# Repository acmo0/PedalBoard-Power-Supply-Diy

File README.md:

# PedalBoard-Alimentation
***
## Table of contents
1. [230V Schematic](#230v-schematic)
2. [Diode Bridge Schematic](#diode-bridge-schematic)
3. [Regulated ouput Schematic](#regulated-output-schematic)
    1. [9V Output](#9v-output)
    2. [9-12V Output](#9-12v-output)
8. [Replicate Project](#replicate-project)
    1. [10 Outputs (7x9v + 3x9-12v) Version](#10-outputs-version)
    2. [7 Outputs (7x9v) Version](#7-outputs-version)
    3. [Custom power supply](#custom-power-supply)
7. [Kicad sources files](#Kicad-sources-files)
8. [Issues](#issues)
***
## 230V Schematic

This is a basic schematic in order to protect your pedalboard against surges (VDR), short-circuit (fuse), electrical noise(EMI filter). You have to use at least a 230/12VAC transformer (best option because it causes less power dissipation on your regulators) and at most 230/18VAC transformer (you have to adapt this limit to your regulators specs). Keep in mind that after the diode brige the voltage is : 

For exemple this is the tension at the output of the diode bridge if your transformer ouput is 18V :

## Diode Bridge Schematic

You connect each transformer outputs (if your transformer have only one secondary coil) on the "From-transformer-secondary-output_X" labels.
There are capacitors in parallel of each diodes to minimize noise from diodes. You have also a 2200µF capacitor to "smooth" the voltage from the diode bridge.
Finaly, you have a 1.85A polyfuse to protect your power supply and pedals mainly against short-circuits. All regulators are connected on "diodes bridge output".

## Regulated Output Schematic
Both regulations can be used in the same power supply. However keep in mind that you have to adapt transformer, diodes for the diodes bridge and polyfuse to the maximum current which can be used by your power supply (and add a margin of course).
### 9V Output

The 4007 diode is used to prevent non-regulated voltage to go into your regulated voltage. C2 and C24 basicaly reduce noise from the regulator. The TVS diode protect your pedals against surges. I suggest to use 1A or 1.5A regulators to minimize thermal dissipation and to have an important margin ( specialy if you want to connect several pedals). Moreover, you have to had a heatsink to your regulator (a piece of aluminium should be enough).
### 9-12V Output

This circuit is based on LM317. You have a switch (or anything else you want which can switch) between 2 resistors. The value of this two resistor is calculted to deliver 9V for the 1.5k resistor and 12v for the 2.15k resistor. You can add an other resistor and change your switch to choose between 9,12, and 18V for exemple. The output voltage of an LM317 in this case is calculated by the relation :

)

In this case, R7 or R8 are R2 and R9 is R1. For exemple, let's calculate Vout for R8 :

=9.06V)

C22 and C33 do the same job as same capacitors for the 9V ouput.

## Replicate Project
### 10 Outputs Version
Here is the schematic. Please note that it's the first version so this schematic and the associated pcb don't include TVS diodes.
The first row contain 9V outputs and the second contain adjustable outputs.

I designed the associated pcb (note that green tracks are jumpers):

If you want to replicate with this exact pcb you can download the [pdf of the pcb](Images/10O/alim-F_Cu.pdf) and use your prefered methode to create pcb. You can also download the [kicad schematic](Sources/10O/alim10o.sch) if you want to create your own pcb design or simply take a look at it. You can also download the [entire kicad project](Sources/10O.zip) with schematic and pcb.
#### Bill of Materials
You can [download it](Sources/10O/alim10o.csv) in csv format
|Ref                                                          |Qnty|Value          |Description                                                                                           |
|-------------------------------------------------------------|----|---------------|------------------------------------------------------------------------------------------------------|
|C1, C3, C5, C7, C9, C11, C13,                                |7   |0.33µF         |Unpolarized capacitor                                                                                 |
|C2, C4, C6, C8, C10, C12, C14, C15, C18, C21, C35, C36, C37, C38, |14  |0.1µF          |Unpolarized capacitor                                                                                 |
|C16, C19, C22,                                               |3   |10µF           |Unpolarized capacitor                                                                                 |
|C24, C25, C26, C27, C28, C29, C30, C31, C32, C33,            |10  |33µF           |Polarized capacitor                                                                                   |
|C34,                                                         |1   |2200µF         |Polarized capacitor, US symbol                                                                        |
|D1, D2, D3, D4, D5, D6, D7, D8, D9, D10, D11, D12, D13,      |13  |1N4007         |Diode                                                                                                 |
|D14, D15, D16, D17,                                          |4   |D_Schottky     |Schottky diode                                                                                        |
|F1,                                                          |1   |Polyfuse       |Resettable fuse, polymeric positive temperature coefficient                                           |
|J1, J2, J3, J4, J5, J6, J7, J8, J9, J10,                     |10  |Barrel_Jack    |DC Barrel Jack                                                                                        |
|J11,                                                         |1   |Conn_01x03_Male|Generic connector, single row, 01x03, script generated (kicad-library-utils/schlib/autogen/connector/)|
|J12, J13, J14,                                               |3   |Conn_01x03_Male|Generic connector, single row, 01x03, script generated (kicad-library-utils/schlib/autogen/connector/)|
|R1, R4, R7,                                                  |3   |2.15k          |Resistor                                                                                              |
|R2, R5, R8,                                                  |3   |1.5k           |Resistor                                                                                              |
|R3, R6, R9,                                                  |3   |240            |Resistor                                                                                              |
|U1, U2, U3, U4, U5, U6, U7,                                  |7   |L7809          |Positive 1.5A 35V Linear Regulator, Fixed Output 9V, TO-220/TO-263/TO-252                             |
|U8, U9, U10,                                                 |3   |LM317          |1.5A 35V Adjustable Linear Regulator, TO-220                                                          |

If you want to replicate this pcb, I advise you to download at least the kicad pcb file to know where are components.

## 7 Outputs version

Here is the [schematic](Images/7O/alim7O.png) :

And the associated [pcb](Images/7O/alim-brd7O.png) (note that green tracks are jumpers) :

If you want to replicate this exact version, you can download the [pdf of the pcb](Images/7O/alim-F_Cu.pdf) or download the [pcb](Sources/7O/alim.kicad_pcb),[schematic](Sourcces/7O/alim.sch) or the [entire kicad project](Sources/7O.zip). I advise you to download at least the [pcb](Images/7O/alim-brd7O.png) or the [kicad pcb file](Sources/7O/alim.kicad_pcb) if you want to replicate this project.

### Bill of material
You can [download it](Sources/7O/BOM-7O.csv) in csv format.
|Ref                                                          |Qnty|Value          |Description                                                                                           |
|-------------------------------------------------------------|----|---------------|------------------------------------------------------------------------------------------------------|
|C1, C3, C5, C7, C9, C11, C14,                                |7   |0.33µF         |Unpolarized capacitor                                                                                 |
|C2, C4, C6, C8, C10, C12, C15, C35, C36, C37, C38,           |11  |0.1µF          |Unpolarized capacitor                                                                                 |
|C13, C16, C24, C25, C26, C27, C28,                           |7   |33µF           |Polarized capacitor                                                                                   |
|C34,                                                         |1   |2200µF         |Polarized capacitorl                                                                                  |
|D1, D2, D3, D4, D5, D6, D7,                                  |7   |1N4007         |Diode                                                                                                 |
|D8, D9, D10, D11, D12, D13, D18,                             |7   |SM6T10A        |10V TVS diode                                                                                         |
|D14, D15, D16, D17,                                          |4   |D_Schottky     |3A Schottky diode                                                                                     |
|F1,                                                          |1   |Polyfuse       |Resettable fuse, polymeric positive temperature coefficient                                           | 
|J1, J2, J3, J4, J5, J6, J7,                                  |7   |Barrel_Jack    |DC Barrel Jack                                                                                        |
|J11,                                                         |1   |Conn_01x03_Male|Generic connector, single row                                                                         |
|U1, U2, U3, U4, U5, U6, U7,                                  |7   |L7809          |Positive 1.5A 35V Linear Regulator, Fixed Output 9V                                                   |

## Kicad Sources files
* 10 outputs files :
    * [schematic](Sources/10O/alim10o.sch)
    * [pcb](Sources/10O/alim10o.kicad_pcb)
    * [bill of materials](Sources/10O/alim10o.csv)
    * [kicad project ( zipped )](Sources/10O.zip)
* 7 outputs files :
    * [schematic](Sources/7O/alim.sch)
    * [pcb](Sources/7O/alim.kicad_pcb)
    * [bill of materials](Sources/7O/BOM-7O.csv)
    * [kicad project ( zipped )](Sources/7O.zip)

## Issues
Please feel free to open an issue if you find an error, want more informations or something else.

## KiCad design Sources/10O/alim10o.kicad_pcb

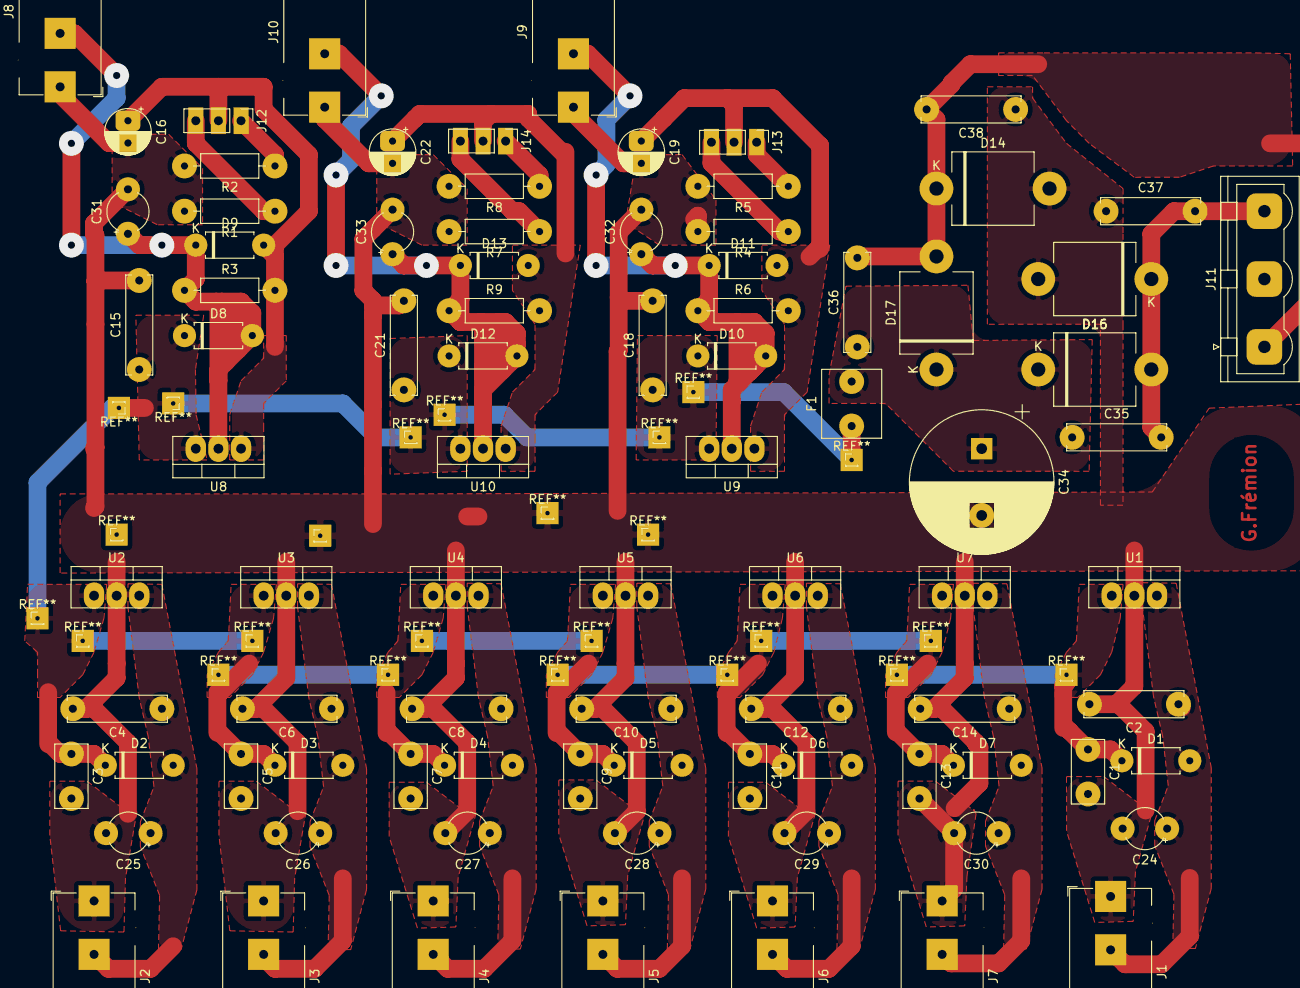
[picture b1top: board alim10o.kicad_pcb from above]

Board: 2 copper layers, 86 parts (0 on the bottom side), 24 nets.

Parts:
C1, C3, C5, C7, C9, C11, C13: 0.33µF; C_Rect_L7.0mm_W3.5mm_P5.00mm
C2, C4, C6, C8, C10, C12, C14, C15, C18, C35, C36, C37, C38: 0.1µF; C_Rect_L11.0mm_W2.8mm_P10.00mm_MKT
C16, C19, C22: 10µF; CP_Radial_D5.0mm_P2.50mm
C21: O.1µF; C_Rect_L11.0mm_W2.8mm_P10.00mm_MKT
C24, C25, C26, C27, C28, C29, C30, C31, C32, C33: 33µF; CP_Radial_Tantal_D4.5mm_P5.00mm
C34: 2200µF; CP_Radial_D16.0mm_P7.50mm
D1, D2, D3, D4, D5, D6, D7, D8, D9, D10, D11, D12, D13: 1N4007; D_A-405_P7.62mm_Horizontal
D14, D15, D16, D17: D_Schottky; D_5KPW_P12.70mm_Horizontal
F1: Polyfuse; C_Rect_L7.5mm_W6.5mm_P5.00mm
J1, J2, J3, J4, J5, J6, J7, J8, J9, J10: Barrel_Jack; BarrelJack_Horizontal
J11: Conn_01x03_Male; PhoenixContact_GMSTBVA_2,5_3-G-7,62_1x03_P7.62mm_Vertical
J12, J13, J14: Conn_01x03_Male; PinHeader_1x03_P2.54mm_Vertical
R1, R4, R7: 2.15k; R_Axial_DIN0207_L6.3mm_D2.5mm_P10.16mm_Horizontal
R2, R5, R8: 1.5k; R_Axial_DIN0207_L6.3mm_D2.5mm_P10.16mm_Horizontal
R3, R6, R9: 240; R_Axial_DIN0207_L6.3mm_D2.5mm_P10.16mm_Horizontal
U1, U2, U3, U4, U5, U6, U7: L7809; TO-220-3_Vertical
U8, U9, U10: LM317; TO-220-3_Vertical

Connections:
GND: C1.2, C2.2, C3.2, C4.2, C5.2, C6.2, C7.2, C8.2, C9.2, C10.2, C11.2, C12.2, C13.2, C14.2, C15.2, C16.2, C18.2, C19.2, C21.2, C22.2, C24.2, C25.2, C26.2, C27.2, C28.2, C29.2, C30.2, C31.2, C32.2, C33.2, C34.2, C37.1, C38.1, D14.2, D15.2, J1.1, J2.1, J3.1, J4.1, J5.1, J6.1, J7.1, J8.1, J9.1, J10.1, R1.2, R2.2, R4.2, R5.2, R7.2, R8.2, U1.2, U2.2, U3.2, U4.2, U5.2, U6.2, U7.2
unnamed: C1.1, C3.1, C5.1, C7.1, C9.1, C11.1, C13.1, C15.1, C18.1, C21.1, D1.1, D2.1, D3.1, D4.1, D5.1, D6.1, D7.1, D8.1, D10.1, D12.1, F1.1, U1.1, U2.1, U3.1, U4.1, U5.1, U6.1, U7.1, U8.3, U9.3, U10.3
unnamed: C2.1, C24.1, D1.2, J1.2, U1.3
unnamed: C10.1, C28.1, D5.2, J5.2, U5.3
unnamed: C12.1, C29.1, D6.2, J6.2, U6.3
unnamed: C14.1, C30.1, D7.2, J7.2, U7.3
unnamed: C16.1, D9.2, J12.2, R3.2, U8.1
unnamed: C19.1, D11.2, J13.2, R6.2, U9.1
unnamed: C22.1, D13.2, J14.2, R9.2, U10.1
unnamed: C4.1, C25.1, D2.2, J2.2, U2.3
unnamed: C6.1, C26.1, D3.2, J3.2, U3.3
unnamed: C8.1, C27.1, D4.2, J4.2, U4.3
unnamed: C31.1, D8.2, D9.1, J8.2, R3.1, U8.2
unnamed: C32.1, D10.2, D11.1, J9.2, R6.1, U9.2
unnamed: C33.1, D12.2, D13.1, J10.2, R9.1, U10.2
unnamed: C34.1, C35.1, C36.1, D16.1, D17.1, F1.2
unnamed: C35.2, C37.2, D15.1, D16.2, J11.3
unnamed: C36.2, C38.2, D14.1, D17.2, J11.1
unnamed: J12.1, R2.1
unnamed: J12.3, R1.1
unnamed: J13.1, R5.1
unnamed: J13.3, R4.1
unnamed: J14.1, R8.1
unnamed: J14.3, R7.1

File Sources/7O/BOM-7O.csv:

Ref,Qnty,Value,Description
"C1, C3, C5, C7, C9, C11, C14, ",7,0.33µF,Unpolarized capacitor
"C2, C4, C6, C8, C10, C12, C15, C35, C36, C37, C38, ",11,0.1µF,Unpolarized capacitor
"C13, C16, C24, C25, C26, C27, C28, ",7,33µF,Polarized capacitor
"C34, ",1,2200µF,Polarized capacitorl
"D1, D2, D3, D4, D5, D6, D7, ",7,1N4007,Diode
"D8, D9, D10, D11, D12, D13, D18, ",7,SM6T10A,10V TVS diode
"D14, D15, D16, D17, ",4,D_Schottky,3A Schottky diode
"F1, ",1,Polyfuse,"Resettable fuse, polymeric positive temperature coefficient"
"J1, J2, J3, J4, J5, J6, J7, ",7,Barrel_Jack,DC Barrel Jack
"J11, ",1,Conn_01x03_Male,"Generic connector, single row"
"U1, U2, U3, U4, U5, U6, U7, ",7,L7809,"Positive 1.5A 35V Linear Regulator, Fixed Output 9V"

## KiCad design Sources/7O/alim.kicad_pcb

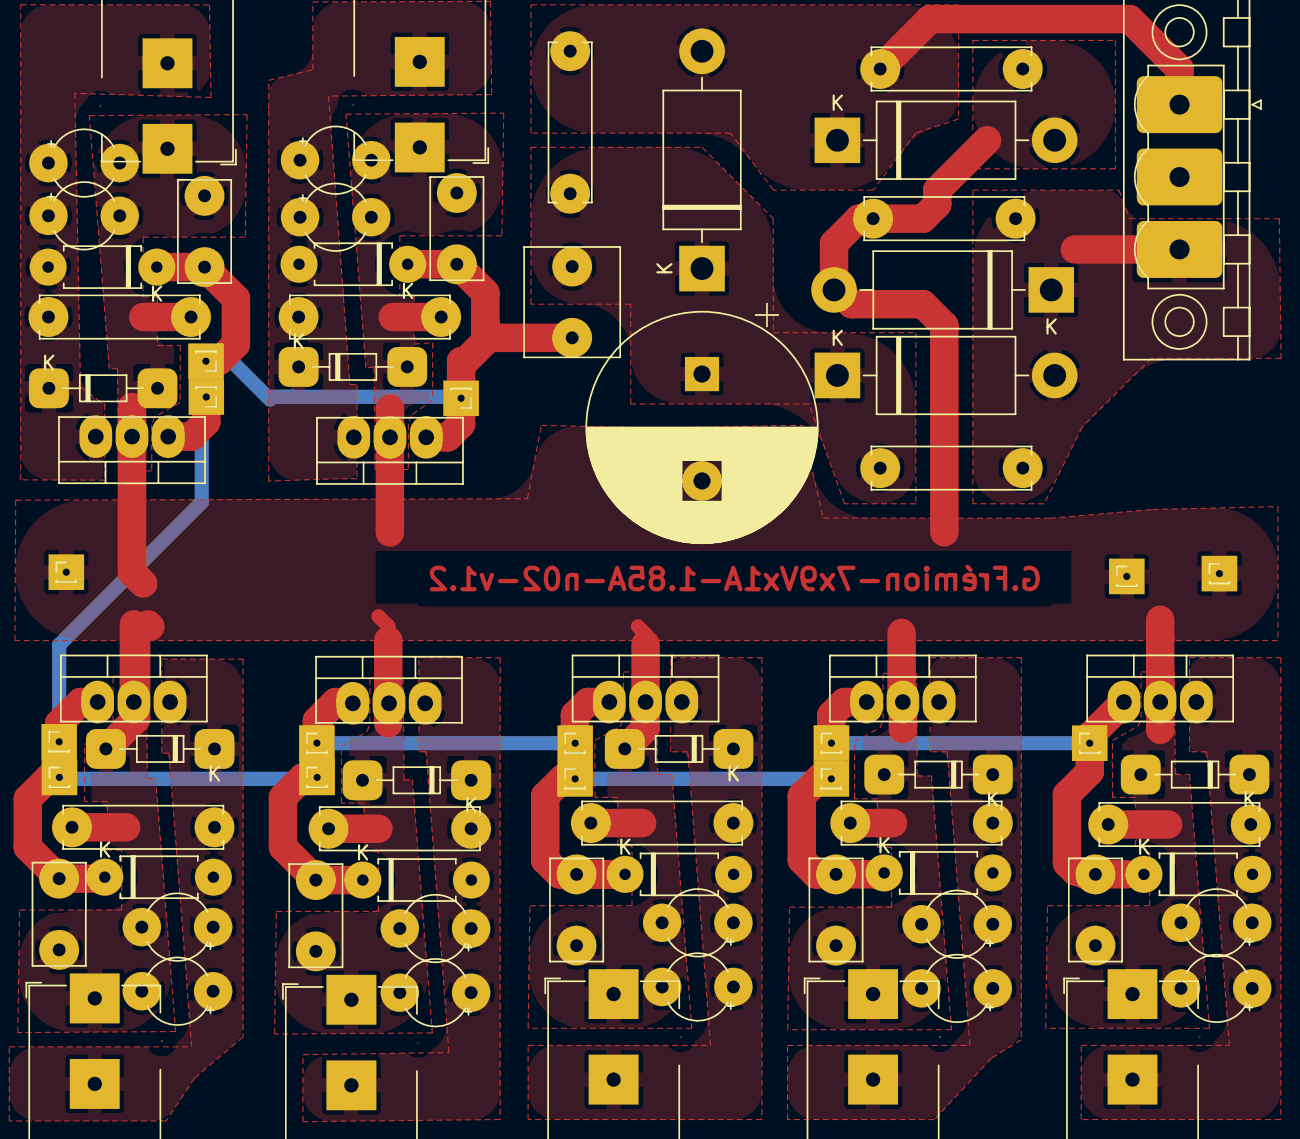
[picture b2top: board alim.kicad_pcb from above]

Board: 2 copper layers, 67 parts (0 on the bottom side), 12 nets.

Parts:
C1, C3, C5, C7, C9, C11, C14: 0.33µF; C_Rect_L7.0mm_W3.5mm_P5.00mm
C2, C4, C6, C8, C10, C12, C15, C35, C36, C37, C38: 0.1µF; C_Rect_L11.0mm_W2.8mm_P10.00mm_MKT
C13, C13#2, C24, C24#2, C25, C25#2, C26, C26#2, C27, C27#2, C28, C28#2, C30, C30#2: 33µF; CP_Radial_Tantal_D4.5mm_P5.00mm
C34: 2200µF; CP_Radial_D16.0mm_P7.50mm
D1, D2, D3, D4, D5, D6, D7: 1N4007; D_A-405_P7.62mm_Horizontal
D8, D10, D11, D12, D13, D18: D_DO-34_SOD68_P7.62mm_Horizontal
D9: SA10A; D_DO-34_SOD68_P7.62mm_Horizontal
D14, D15, D16, D17: D_Schottky; D_DO-201AD_P15.24mm_Horizontal
F1: Polyfuse; C_Rect_L7.5mm_W6.5mm_P5.00mm
J1, J2, J3, J4, J5, J6, J7: Barrel_Jack; BarrelJack_Horizontal
J11: Conn_01x03_Male; PhoenixContact_MSTBV_2,5_3-GF-5,08_1x03_P5.08mm_Vertical_Th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
U1, U2, U3, U4, U5, U6, U7: L7809; TO-220-3_Vertical

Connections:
GND: C1.2, C2.2, C3.2, C4.2, C5.2, C6.2, C7.2, C8.2, C9.2, C10.2, C11.2, C12.2, C13.2, C13#2.2, C14.2, C15.2, C24.2, C24#2.2, C25.2, C25#2.2, C26.2, C26#2.2, C27.2, C27#2.2, C28.2, C28#2.2, C30.2, C30#2.2, C34.2, C37.1, C38.1, D8.2, D9.2, D10.2, D11.2, D12.2, D13.2, D14.2, D15.2, D18.2, J1.1, J2.1, J3.1, J4.1, J5.1, J6.1, J7.1, U1.2, U2.2, U3.2, U4.2, U5.2, U6.2, U7.2
unnamed: C1.1, C3.1, C5.1, C7.1, C9.1, C11.1, C14.1, D1.1, D2.1, D3.1, D4.1, D5.1, D6.1, D7.1, F1.1, U1.1, U2.1, U3.1, U4.1, U5.1, U6.1, U7.1
unnamed: C2.1, C24.1, C24#2.1, D1.2, D9.1, J1.2, U1.3
unnamed: C10.1, C28.1, C28#2.1, D5.2, D13.1, J5.2, U5.3
unnamed: C12.1, C13.1, C13#2.1, D6.2, D8.1, J6.2, U6.3
unnamed: C15.1, C30.1, C30#2.1, D7.2, D10.1, J7.2, U7.3
unnamed: C4.1, C25.1, C25#2.1, D2.2, D11.1, J2.2, U2.3
unnamed: C6.1, C26.1, C26#2.1, D3.2, D12.1, J3.2, U3.3
unnamed: C8.1, C27.1, C27#2.1, D4.2, D18.1, J4.2, U4.3
unnamed: C34.1, C35.1, C36.1, D16.1, D17.1, F1.2
unnamed: C35.2, C37.2, D15.1, D16.2, J11.3
unnamed: C36.2, C38.2, D14.1, D17.2, J11.1

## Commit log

2021-11-30 Rename alim10o to alim10o.html
